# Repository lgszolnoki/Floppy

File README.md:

**Floppy ReadMe** \
Laszlo Szolnoki  ([test@szolnoki.eu](mailto:test@szolnoki.eu)) \
15 June 2024

# Overview

2023 I got a couple of 5.25" floppy disk from the late 80s. All used in earlier PCs built in the GDR with corresponding formating. 
My first attempts to hande them with a modern PC failed. So I decided to build a CP/M 2.2 based retro computer. 
I learned RomWBW and was immediately determined to use it as my software base. # Overview

# Floppy

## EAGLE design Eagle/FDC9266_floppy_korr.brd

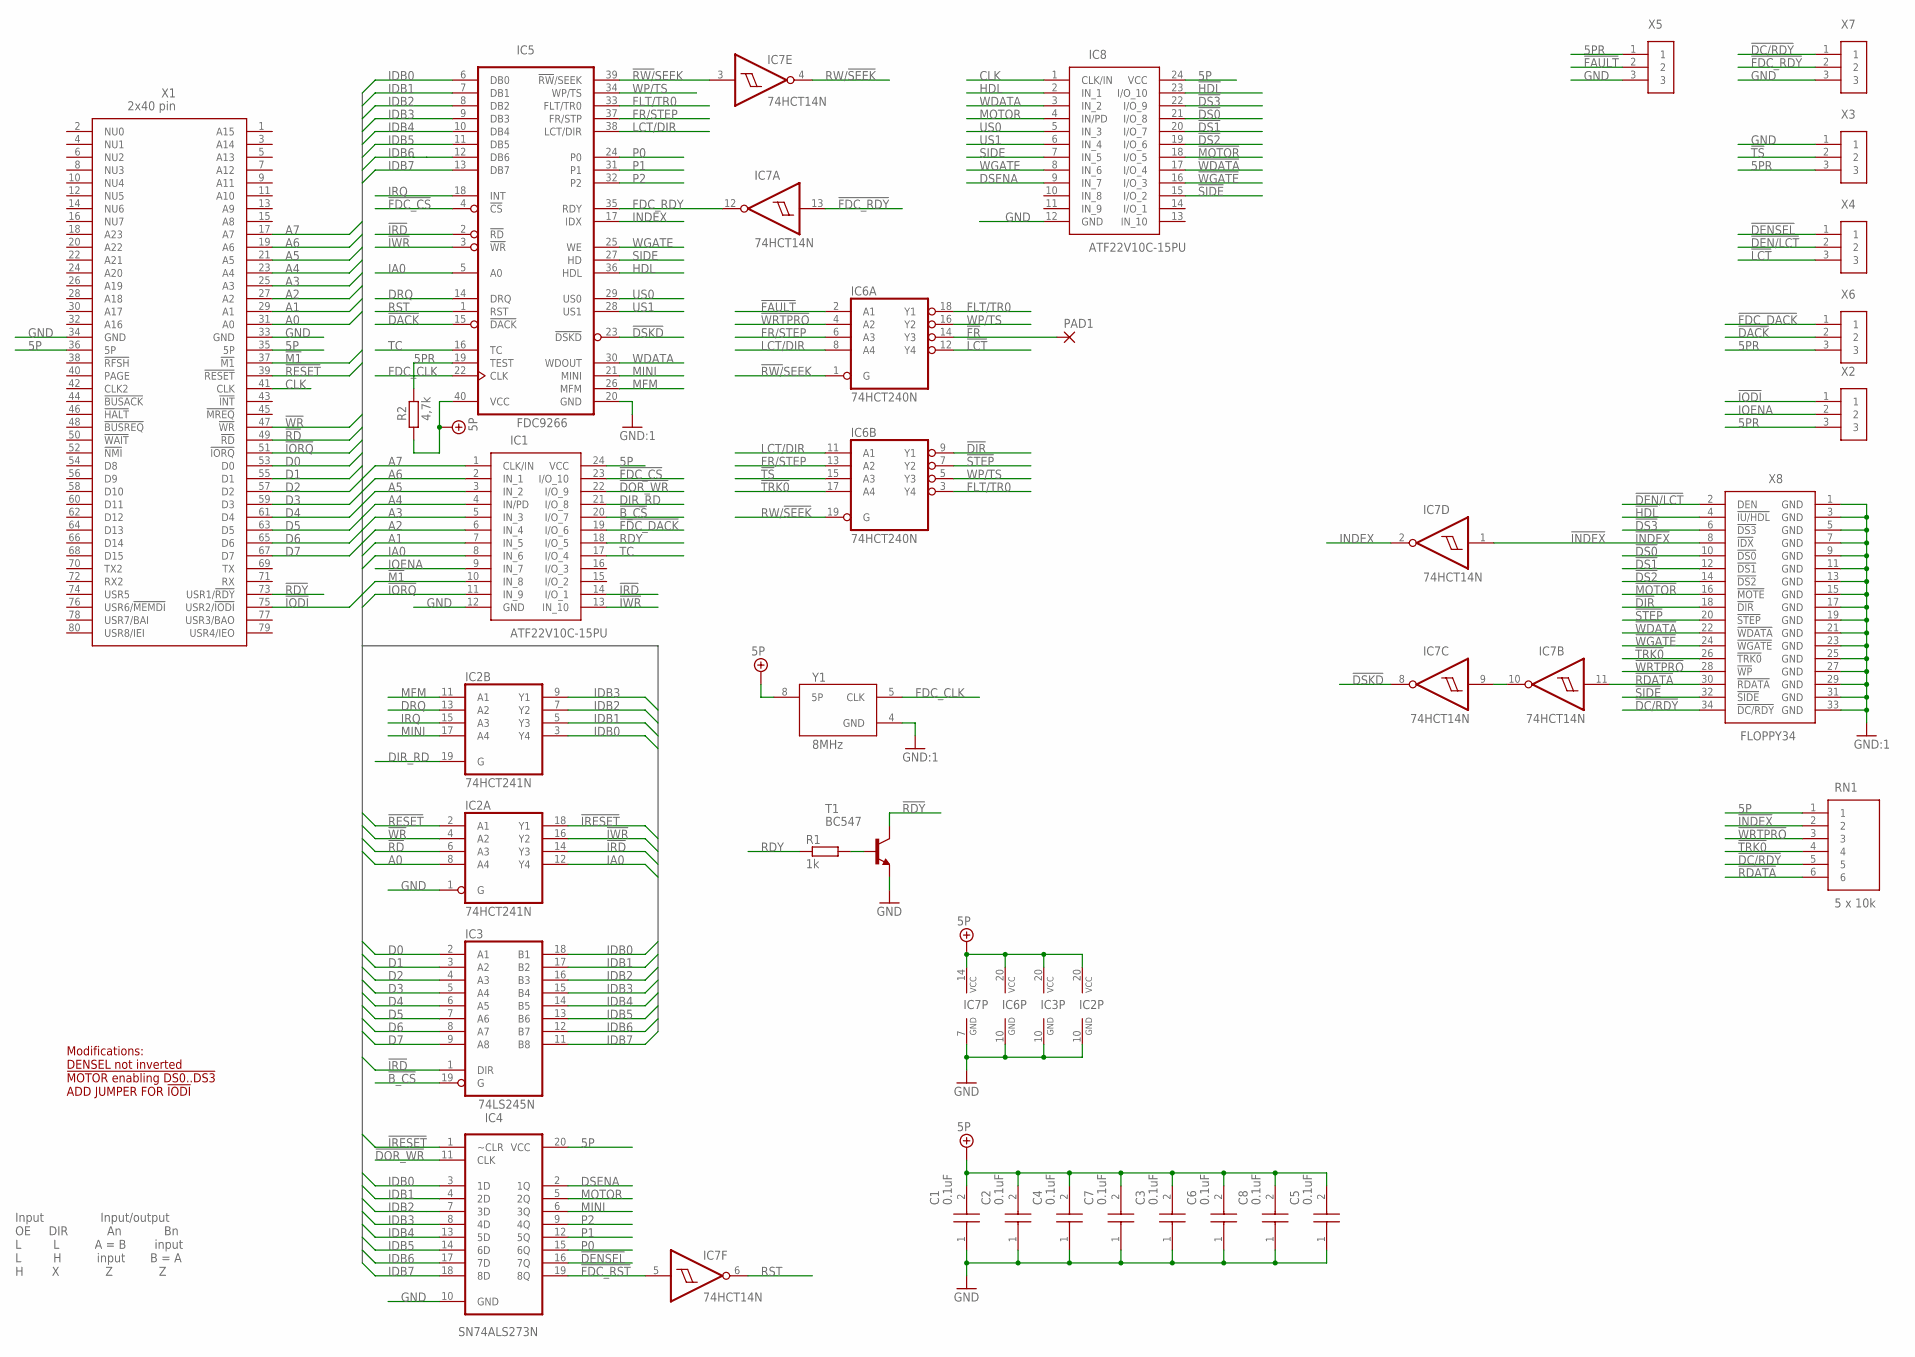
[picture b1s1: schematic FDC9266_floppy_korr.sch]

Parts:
C1, C2, C3, C4, C5, C6, C7, C8: 0.1uF; C315C103K5R5TA7303
IC1, IC8: ATF22V10C-15PU; DIP794W56P254L3188H533Q24N
IC2: 74HCT241N; DIL20
IC3: 74LS245N; DIL20
IC4: SN74ALS273N; DIP254P762X508-20
IC5: FDC9266; DIP1550W53P254L5232H424Q40N
IC6: 74HCT240N; DIL20
IC7: 74HCT14N; DIL14
PAD1: WIREPAD1,6/0,8; 1,6/0,8
R1: 1k; 0207/10
R2: 4,7k; 0207/10
RN1: 5 x 10k; 4606X102103LF
T1: BC547; TO92
X1: 2x40 pin; RC2014_80_RA
X2, X3, X4, X5, X6, X7: TSW-103-07-G-S07; TSW-103-XX-G-S
X8: FLOPPY34; 09185346323
Y1: 8MHz; ECS-2100AX-200

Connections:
5P: C1.2, C2.2, C3.2, C4.2, C5.2, C6.2, C7.2, C8.2, IC1.24 (VCC), IC2.20 (VCC), IC3.20 (VCC), IC4.20 (VCC), IC5.40 (VCC), IC6.20 (VCC), IC7.14 (VCC), IC8.24 (VCC), R2.1, RN1.1, X1.35 (5P), X1.36 (5P), Y1.8 (5P)
5PR: IC5.19 (TEST), R2.2, X2.3, X3.3, X5.1, X6.3
!B_CS: IC1.20 (I/O_7), IC3.19 (G)
!DACK: IC5.15 (!DACK), X6.2
!DC/RDY: RN1.5, X7.1, X8.34 (!DC/RDY)
!DEN/LCT: X4.2, X8.2 (DEN)
!DENSEL: IC4.16 (7Q), X4.1
!DIR: IC6.9 (Y1), X8.18 (!DIR)
!DOR_WR: IC1.22 (I/O_9), IC4.11 (CLK)
!DS0: IC8.21 (I/O_8), X8.10 (!DS0)
!DS1: IC8.20 (I/O_7), X8.12 (!DS1)
!DS2: IC8.19 (I/O_6), X8.14 (!DS2)
!DS3: IC8.22 (I/O_9), X8.6 (!DS3)
!DSKD: IC5.23 (!DSKD), IC7.8 (O)
!FAULT: IC6.2 (A1), X5.2
!FDC_CS: IC1.23 (I/O_10), IC5.4 (!CS)
!FDC_DACK: IC1.19 (I/O_6), X6.1
!FDC_RDY: IC7.13 (I), X7.2
!FDC_RST: IC4.19 (8Q), IC7.5 (I)
!FR: IC6.14 (Y3), PAD1.1
!HDL: IC8.23 (I/O_10), X8.4 (!IU/HDL)
!INDEX: IC7.1 (I), RN1.2, X8.8 (!IDX)
!IODI: X1.75 (USR2/!IODI), X2.1
!IORQ: IC1.11 (IN_9), X1.51 (!IORQ)
!IRD: IC1.14 (I/O_1), IC2.14 (Y3), IC3.1 (DIR), IC5.2 (!RD)
!IRESET: IC2.18 (Y1), IC4.1 (~CLR)
!IWR: IC1.13 (IN_10), IC2.16 (Y2), IC5.3 (!WR)
!LCT: IC6.12 (Y4), X4.3
!M1: IC1.10 (IN_8), X1.37 (!M1)
!MOTOR: IC8.18 (I/O_5), X8.16 (!MOTE)
!RD: IC2.6 (A3), X1.49 (!RD)
!RDATA: IC7.11 (I), RN1.6, X8.30 (!RDATA)
!RDY: T1.3 (C), X1.73 (USR1/!RDY)
!RESET: IC2.2 (A1), X1.39 (!RESET)
!RW/!SEEK: IC5.39 (!RW!/SEEK), IC6.1 (G), IC7.3 (I)
!SIDE: IC8.15 (I/O_2), X8.32 (!SIDE)
!STEP: IC6.7 (Y2), X8.20 (!STEP)
!TRK0: IC6.17 (A4), RN1.4, X8.26 (!TRK0)
!TS: IC6.15 (A3), X3.2
!WDATA: IC8.17 (I/O_4), X8.22 (!WDATA)
!WGATE: IC8.16 (I/O_3), X8.24 (!WGATE)
!WR: IC2.4 (A2), X1.47 (!WR)
!WRTPRO: IC6.4 (A2), RN1.3, X8.28 (!WP)
A0: IC2.8 (A4), X1.31 (A0)
A1: IC1.7 (IN_5), X1.29 (A1)
A2: IC1.6 (IN_4), X1.27 (A2)
A3: IC1.5 (IN_3), X1.25 (A3)
A4: IC1.4 (IN/PD), X1.23 (A4)
A5: IC1.3 (IN_2), X1.21 (A5)
A6: IC1.2 (IN_1), X1.19 (A6)
A7: IC1.1 (CLK/IN), X1.17 (A7)
CLK: IC8.1 (CLK/IN), X1.41 (CLK)
D0: IC3.2 (A1), X1.53 (D0)
D1: IC3.3 (A2), X1.55 (D1)
D2: IC3.4 (A3), X1.57 (D2)
D3: IC3.5 (A4), X1.59 (D3)
D4: IC3.6 (A5), X1.61 (D4)
D5: IC3.7 (A6), X1.63 (D5)
D6: IC3.8 (A7), X1.65 (D6)
D7: IC3.9 (A8), X1.67 (D7)
DIR_RD: IC1.21 (I/O_8), IC2.19 (G)
DRQ: IC2.13 (A2), IC5.14 (DRQ)
DSENA: IC4.2 (1Q), IC8.9 (IN_7)
FDC_CLK: IC5.22 (CLK), Y1.5 (CLK)
FDC_RDY: IC5.35 (RDY), IC7.12 (O)
FLT/TR0: IC5.33 (FLT/TR0), IC6.3 (Y4), IC6.18 (Y1)
FR/STEP: IC5.37 (FR/STP), IC6.6 (A3), IC6.13 (A2)
GND: C1.1, C2.1, C3.1, C4.1, C5.1, C6.1, C7.1, C8.1, IC1.12 (GND), IC2.1 (G), IC2.10 (GND), IC3.10 (GND), IC4.10 (GND), IC5.20 (GND), IC6.10 (GND), IC7.7 (GND), IC8.12 (GND), T1.1 (E), X1.33 (GND), X1.34 (GND), X3.1, X5.3, X7.3, X8.1 (GND), X8.3 (GND), X8.5 (GND), X8.7 (GND), X8.9 (GND), X8.11 (GND), X8.13 (GND), X8.15 (GND), X8.17 (GND), X8.19 (GND), X8.21 (GND), X8.23 (GND), X8.25 (GND), X8.27 (GND), X8.29 (GND), X8.31 (GND), X8.33 (GND), Y1.4 (GND)
HDL: IC5.36 (HDL), IC8.2 (IN_1)
IA0: IC1.8 (IN_6), IC2.12 (Y4), IC5.5 (A0)
IDB0: IC2.3 (Y4), IC3.18 (B1), IC4.3 (1D), IC5.6 (DB0)
IDB1: IC2.5 (Y3), IC3.17 (B2), IC4.4 (2D), IC5.7 (DB1)
IDB2: IC2.7 (Y2), IC3.16 (B3), IC4.7 (3D), IC5.8 (DB2)
IDB3: IC2.9 (Y1), IC3.15 (B4), IC4.8 (4D), IC5.9 (DB3)
IDB4: IC3.14 (B5), IC4.13 (5D), IC5.10 (DB4)
IDB5: IC3.13 (B6), IC4.14 (6D), IC5.11 (DB5)
IDB6: IC3.12 (B7), IC4.17 (7D), IC5.12 (DB6)
IDB7: IC3.11 (B8), IC4.18 (8D), IC5.13 (DB7)
INDEX: IC5.17 (IDX), IC7.2 (O)
IOENA: IC1.9 (IN_7), X2.2
IRQ: IC2.15 (A3), IC5.18 (INT)
LCT/DIR: IC5.38 (LCT/DIR), IC6.8 (A4), IC6.11 (A1)
MFM: IC2.11 (A1), IC5.26 (MFM)
MINI: IC2.17 (A4), IC4.6 (3Q), IC5.21 (MINI)
MOTOR: IC4.5 (2Q), IC8.4 (IN/PD)
unnamed: IC7.9 (I), IC7.10 (O)
unnamed: R1.2, T1.2 (B)
P0: IC4.15 (6Q), IC5.24 (P0)
P1: IC4.12 (5Q), IC5.31 (P1)
P2: IC4.9 (4Q), IC5.32 (P2)
RDY: IC1.18 (I/O_5), R1.1
RST: IC5.1 (RST), IC7.6 (O)
RW/!SEEK: IC6.19 (G), IC7.4 (O)
SIDE: IC5.27 (HD), IC8.7 (IN_5)
TC: IC1.17 (I/O_4), IC5.16 (TC)
US0: IC5.29 (US0), IC8.5 (IN_3)
US1: IC5.28 (US1), IC8.6 (IN_4)
WDATA: IC5.30 (WDOUT), IC8.3 (IN_2)
WGATE: IC5.25 (WE), IC8.8 (IN_6)
WP/TS: IC5.34 (WP/TS), IC6.5 (Y3), IC6.16 (Y2)

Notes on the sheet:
Input Input/output OE DIR An Bn L L A = B input L H input B = A H X Z Z
Modifications: DENSEL not inverted !MOTOR enabling DS0..DS3 ADD JUMPER FOR !IODI

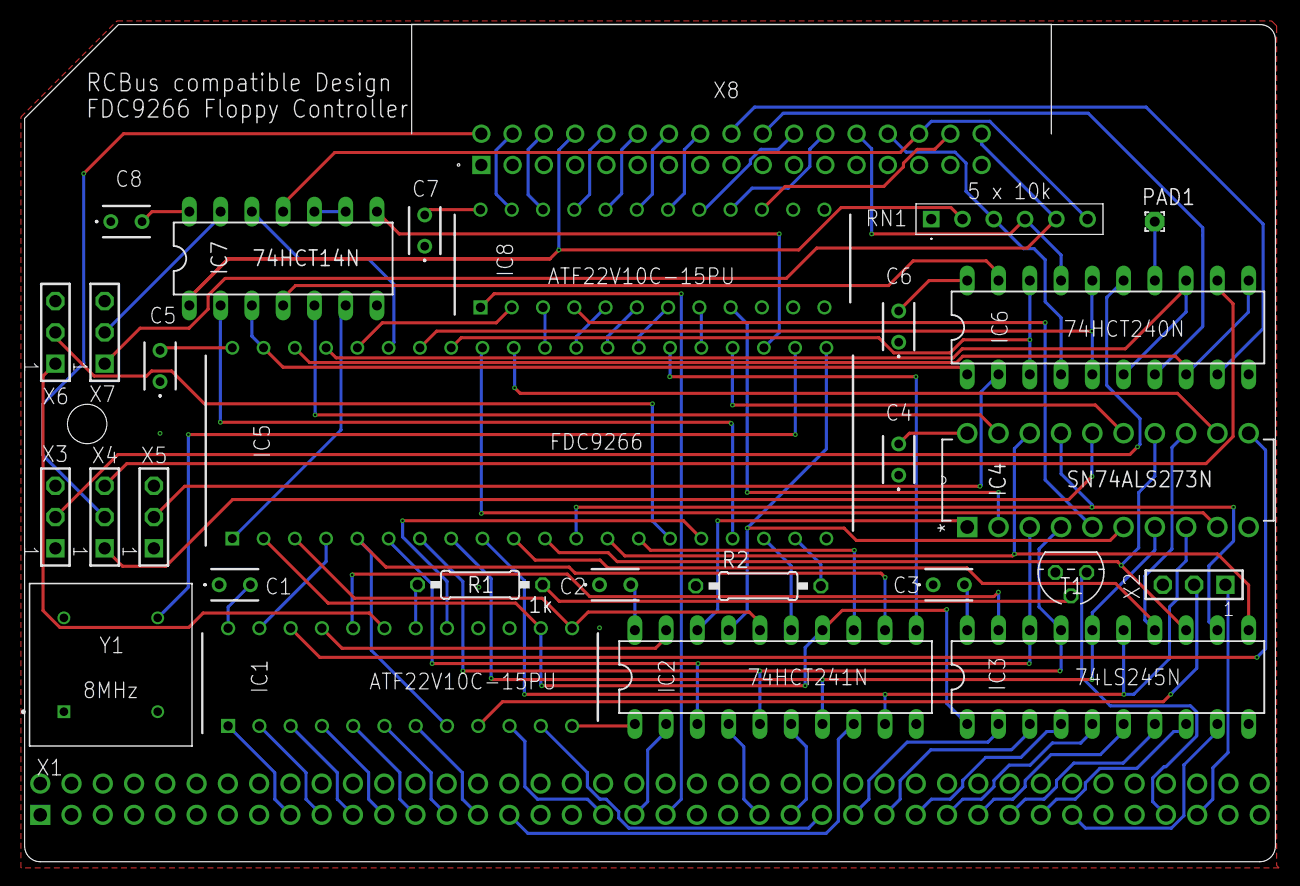
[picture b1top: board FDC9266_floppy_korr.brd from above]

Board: 4 copper layers, 101.6 x 68.0 mm, 30 parts (0 on the bottom side), 100 nets.

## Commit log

2024-06-15 Update LICENSE
2024-06-15 Create enclosure
2024-06-15 Rename FloppyTower Drawing v1.pdf to FloppyTower Drawing.pdf
2024-06-17 Add files via upload
    final version
